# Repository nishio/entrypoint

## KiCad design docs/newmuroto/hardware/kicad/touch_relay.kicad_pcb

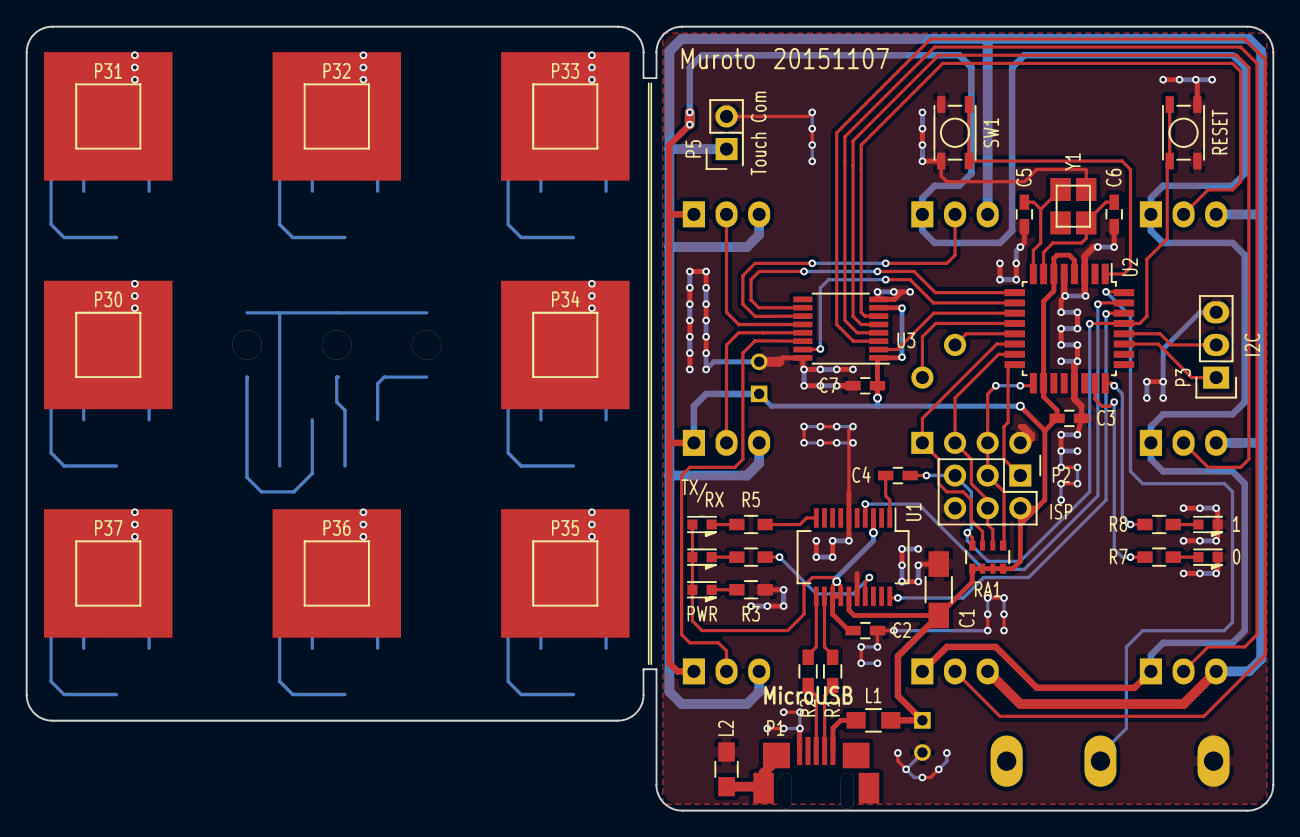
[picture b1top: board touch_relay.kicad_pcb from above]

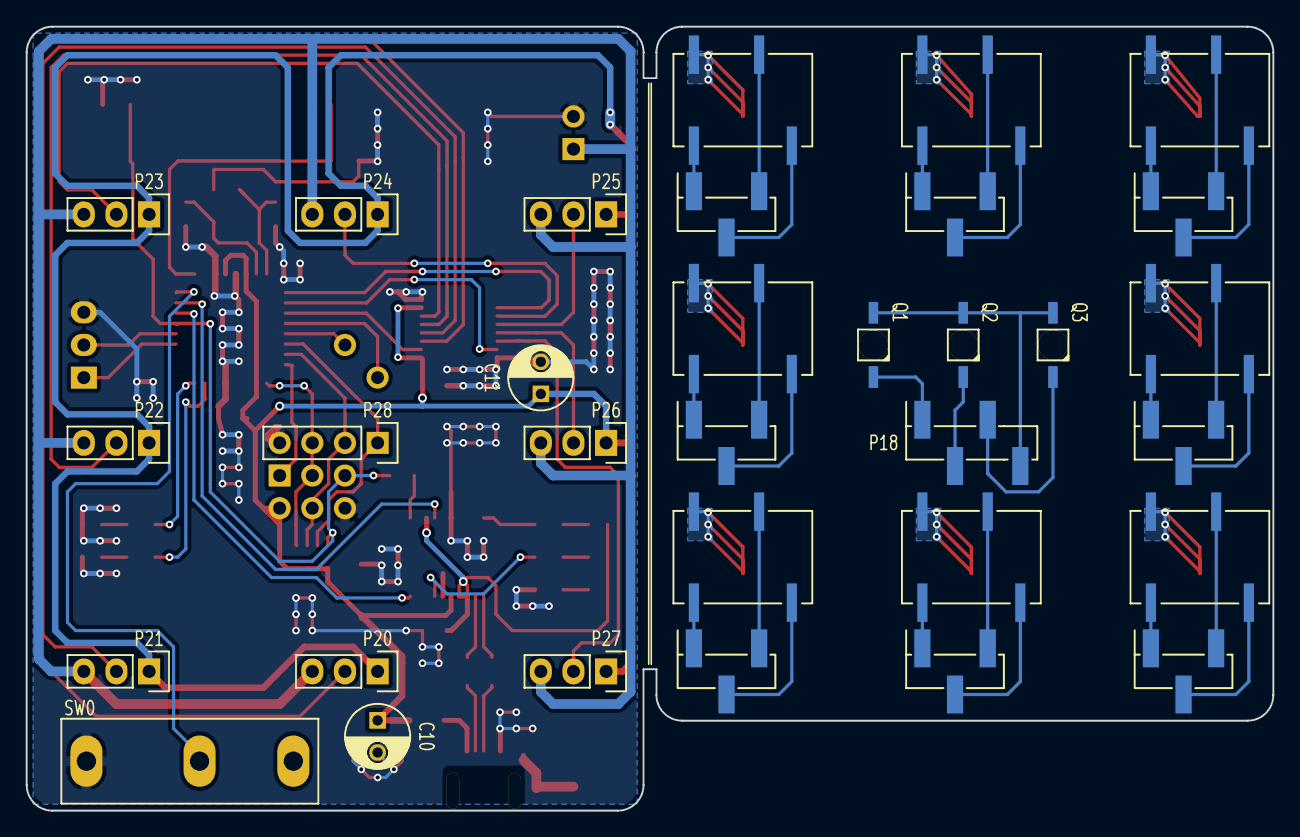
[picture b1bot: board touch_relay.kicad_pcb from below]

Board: 2 copper layers, 97.0 x 61.0 mm, 74 parts (32 on the bottom side), 82 nets.

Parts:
C1: 10u; C_1206_HandSoldering
C2, C3, C4, C7: 0.1u; C_0603_HandSoldering
C5, C6: 22p; C_0603_HandSoldering
C10, C11: 100u; C_Radial_D5_L6_P2.5
D1: PWR; LED-0603-1
D2: RXD; LED-0603-1
D3: TXD; LED-0603-1
D4: ST1; LED-0603-1
D5: ST2; LED-0603-1
L1, L2: Ferrite; R_0805_HandSoldering
P1: MicroUSB; USB_ZX62R-B-5P-N
P2: ISP; Pin_Header_Straight_2x03
P3: I2C; Pin_Header_Straight_1x03
P4: Switch; Switch_SS-PD
P5: Header; Pin_Header_Straight_2x01
P10, P11, P12, P13, P14, P15, P16, P17: Header; Pin_Header_SMD_1x03
P18: Header; Pin_Header_SMD_1x04
P20, P21, P22, P23, P24, P25, P26, P27: Header; Pin_Header_Straight_1x03
P28: Header; Pin_Header_Straight_1x04
P30, P31, P32, P33, P34, P35, P36, P37: TOUCH; 1Pin
P42, P43: PIN; 1Pin
Q1, Q2, Q3: OPTTR; OPTTR_VEMT2500
R1, R2: 27; R_0603_HandSoldering
R3, R7, R8: 1k; R_0603_HandSoldering
R4, R5: 470; R_0603_HandSoldering
RA1: 10k; R_Array_Convex_4x0603
SW1: SW1; Switch_SKRPACE010
SW2: RESET; Switch_SKRPACE010
U1: FT231XS; SSOP-20_4.0x8.5mm_Pitch0.635mm
U2: ATMEGA328P-A; TQFP-32_7x7mm_Pitch0.8mm
U3: NPIC6C595; TSSOP-16_4.4x5mm_Pitch0.65mm
U10, U11, U12, U13, U14, U15, U16, U17: RELAY_1FormA; Relay_G6L
Y1: 16MHz; crystal_FA238-TSX3225

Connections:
/FT3V3: C2.1, D1.2, D2.2, D3.2, U1.3, U1.13, U1.14
/FT->AVR: U1.20, U2.30
/FT<-AVR: U1.4, U2.31
/K0: P28.1, RA1.7, U2.14
/K1: P2.4, P28.2, RA1.6, U2.15
/K2: P2.3, P28.3, RA1.5, U2.17
/RESET: C4.2, P2.5, RA1.8, SW2.1, U2.29
/SCL: P3.2, U2.28
/SDA: P3.1, U2.27
/SH_DS: U2.11, U3.2
/SH_SHCP: U2.10, U3.15
/SH_STCP: U2.9, U3.10
/SW0: P4.2, U2.32
/SW1: SW1.1, U2.1
/TOUCH_COM: P5.1, P20.3, P21.3, P22.3, P23.3, P24.3, P25.3, P26.3, P27.3
GND: C1.2, C2.2, C3.2, C5.2, C6.2, C7.2, C10.2, C11.2, D4.1, D5.1, L2.2, P1.5, P2.6, P3.3, P4.1, P5.2, P28.4, R3.1, SW1.2, SW2.2, U1.6, U1.16, U2.3, U2.5, U2.21, U3.8, U3.16
unnamed: C4.1, U1.1
unnamed: C5.1, U2.8, Y1.2
unnamed: C6.1, U2.7, Y1.1
unnamed: D1.1, R3.2
unnamed: D2.1, R4.2
unnamed: D3.1, R5.2
unnamed: D4.2, R7.1
unnamed: D5.2, R8.1
unnamed: L1.2, P1.1
unnamed: L2.1, P1.M2, P1.M3
unnamed: P1.2, R1.2
unnamed: P1.3, R2.2
unnamed: P2.1, U2.16
unnamed: P10.1, U10.3
unnamed: P10.2, U10.4
unnamed: P10.3, U10.1
unnamed: P11.1, U11.3
unnamed: P11.2, U11.4
unnamed: P11.3, U11.1
unnamed: P12.1, U12.3
unnamed: P12.2, U12.4
unnamed: P12.3, U12.1
unnamed: P13.1, U13.3
unnamed: P13.2, U13.4
unnamed: P13.3, U13.1
unnamed: P14.1, U14.3
unnamed: P14.2, U14.4
unnamed: P14.3, U14.1
unnamed: P15.1, U15.3
unnamed: P15.2, U15.4
unnamed: P15.3, U15.1
unnamed: P16.1, U16.3
unnamed: P16.2, U16.4
unnamed: P16.3, U16.1
unnamed: P17.1, U17.3
unnamed: P17.2, U17.4
unnamed: P17.3, U17.1
unnamed: P18.1, Q1.3
unnamed: P18.2, Q2.3
unnamed: P18.3, Q3.3
unnamed: P18.4, Q1.1, Q2.1, Q3.1
unnamed: P20.2, U3.3
unnamed: P21.2, U3.4
unnamed: P22.2, U3.5
unnamed: P23.2, U3.6
unnamed: P24.2, U3.11
unnamed: P25.2, U3.12
unnamed: P26.2, U3.13
unnamed: P27.2, U3.14
unnamed: P30.1, U10.2
unnamed: P31.1, U11.2
unnamed: P32.1, U12.2
unnamed: P33.1, U13.2
unnamed: P34.1, U14.2
unnamed: P35.1, U15.2
unnamed: P36.1, U16.2
unnamed: P37.1, U17.2
unnamed: P42.1, U2.12
unnamed: P43.1, U2.13
unnamed: R1.1, U1.12
unnamed: R2.1, U1.11
unnamed: R4.1, U1.17
unnamed: R5.1, U1.10
unnamed: R7.2, U2.23
unnamed: R8.2, U2.24
VCC: C1.1, C3.1, C7.1, C10.1, C11.1, L1.1, P2.2, P20.1, P21.1, P22.1, P23.1, P24.1, P25.1, P26.1, P27.1, RA1.1, RA1.2, RA1.3, RA1.4, U1.15, U2.4, U2.6, U2.18, U3.1, U3.7

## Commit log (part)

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2026-01-24 Minimal snapshot: profile pages
2026-01-24 Update profile pages and add GitHub Pages config
2026-01-24 Fix relative paths for GitHub Pages
2026-01-25 Restructure profiles and split history pages
